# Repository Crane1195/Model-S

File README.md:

# Model-S
This circuit board is a complete solution for making custom all digital GameCube controllers without soldering.

## Features
- Connects to GameCube/Wii/GCC to USB adapter using the USB-C to GameCube cables that are sold on the Frame1 and the B0XX websites
- Connect buttons with screw terminals or 2.54mm pitch through holes
- Easily connect to a Brook Board to use the controller on PlayStation/Xbox/other consoles, with both boards sharing the Model S USB-C port
- Can be powered with just 3.3V, allowing the board to work on Mayflash adapters without the gray USB cable as well as GameCube/Wii consoles with faulty rumble lines

## Resources

User Manual - https://www.craneslab.xyz/manuals/s

Firmware - https://github.com/Crane1195/CL-FW

Questions - https://craneslab.xyz/discord

## License
This project is licenced under the GNU GPL Version 3. [See the included LICENSE file for details](LICENSE).

## Support my work
I set up a donation link for people who appreciate my work and wish to donate. Donations are greatly appreciated, but are far from necessary:

https://www.paypal.com/donate/?hosted_button_id=NFDEML5FKR8N8

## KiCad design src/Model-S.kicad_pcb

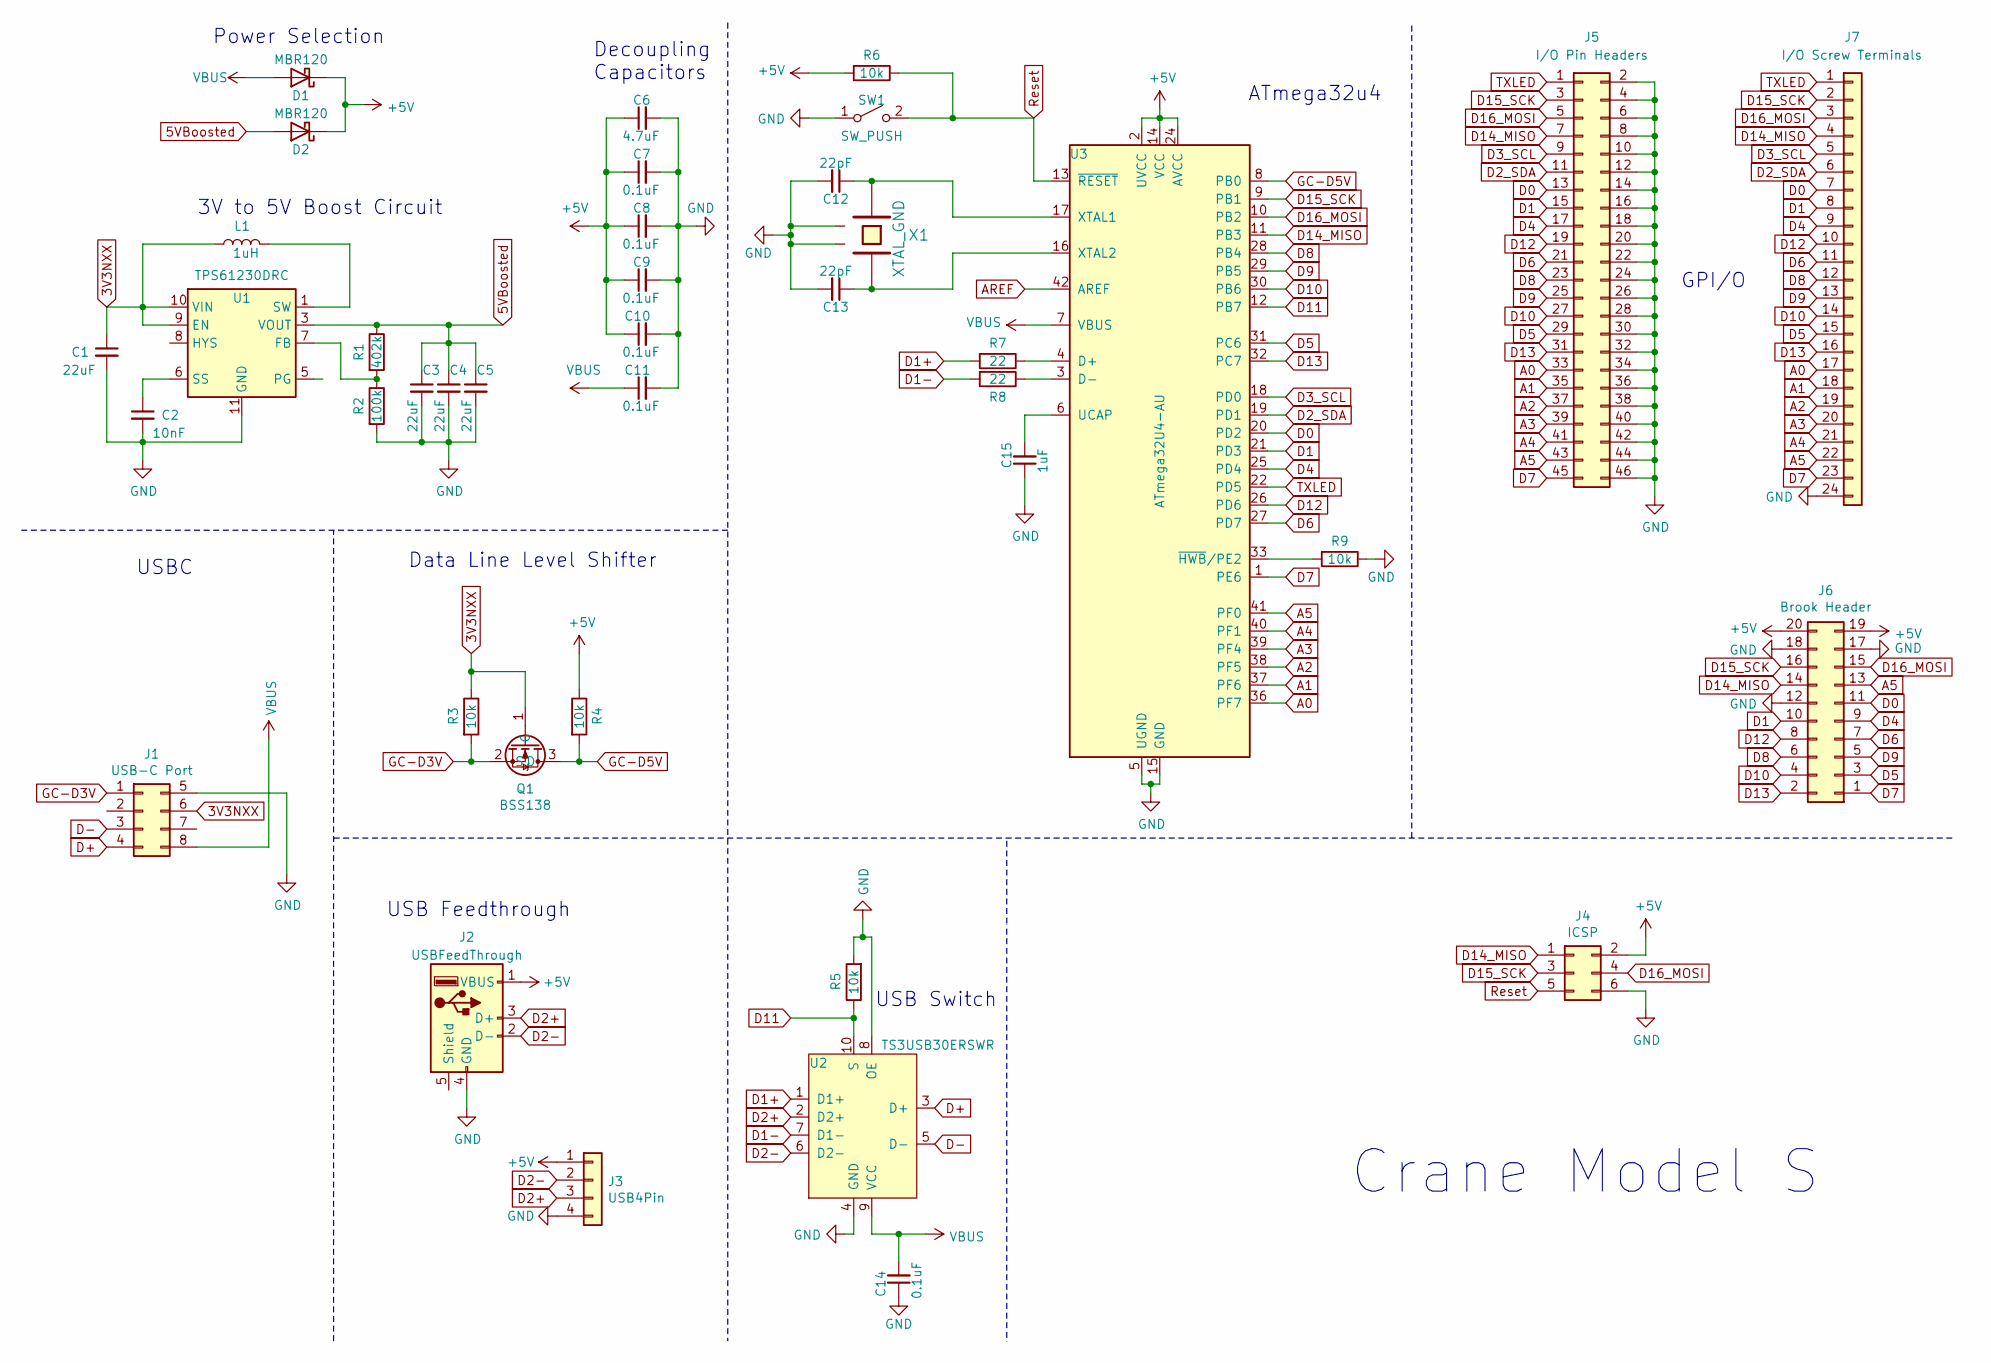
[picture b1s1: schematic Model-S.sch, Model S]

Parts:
C1, C3, C4, C5: 22uF; C_0805_2012Metric_Pad1.18x1.45mm_HandSolder
C2: 10nF; C_0805_2012Metric_Pad1.18x1.45mm_HandSolder
C6: 4.7uF; C_0805_2012Metric_Pad1.18x1.45mm_HandSolder
C7, C8, C9, C10, C11, C14: 0.1uF; C_0805_2012Metric_Pad1.18x1.45mm_HandSolder
C12, C13: 22pF; C_0805_2012Metric_Pad1.18x1.45mm_HandSolder
C15: 1uF; C_0805_2012Metric_Pad1.18x1.45mm_HandSolder
D1, D2: MBR120; D_SOD-123
J1: USB-C Port; Crane_USBC
J2: USBFeedThrough; USB_A_Female_UE27AC54100
J3: USB4Pin; PinHeader_1x04_P2.54mm_Vertical
J4: ICSP; PinHeader_2x03_P2.54mm_Vertical
J5: I/O Pin Headers; PinHeader_2x23_P2.54mm_Vertical
J6: Brook Header; PinHeader_2x10_P2.54mm_Vertical
J7: I/O Screw Terminals; 24PinScrewTerminal
L1: 1uH; L_1008_2520Metric
Q1: BSS138; SOT-23
R1: 402k; R_0805_2012Metric_Pad1.20x1.40mm_HandSolder
R2: 100k; R_0805_2012Metric_Pad1.20x1.40mm_HandSolder
R3, R4, R5, R6, R9: 10k; R_0805_2012Metric_Pad1.20x1.40mm_HandSolder
R7, R8: 22; R_0805_2012Metric_Pad1.20x1.40mm_HandSolder
SW1: SW_PUSH; SW_SPST_TL3342
U1: TPS61230DRC; Texas_S-PVSON-N10_ThermalVias
U2: TS3USB30ERSWR; UQFN-10_1.4x1.8mm_P0.4mm
U3: ATmega32U4-AU; TQFP-44_10x10mm_P0.8mm
X1: XTAL_GND; Crystal_SMD_TXC_7M-4Pin_3.2x2.5mm

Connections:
3V3NXX: C1.1, J1.6, L1.1, Q1.1 (G), R3.1, U1.9 (EN), U1.10 (VIN)
5VBoosted: C3.1, C4.1, C5.1, D2.2 (A), R1.1, U1.3 (VOUT), U1.4 (VOUT)
+5V: C6.1, C7.1, C8.1, C9.1, C10.1, D1.1 (K), D2.1 (K), J2.1 (VBUS), J3.1, J4.2, J6.19, J6.20, R4.1, R6.2, U3.2 (UVCC), U3.14 (VCC), U3.24 (AVCC), U3.34 (VCC), U3.44 (AVCC)
A0: J5.33, J7.17, U3.36 (PF7)
A1: J5.35, J7.18, U3.37 (PF6)
A2: J5.37, J7.19, U3.38 (PF5)
A3: J5.39, J7.20, U3.39 (PF4)
A4: J5.41, J7.21, U3.40 (PF1)
A5: J5.43, J6.13, J7.22, U3.41 (PF0)
AREF: U3.42 (AREF)
D0: J5.13, J6.11, J7.7, U3.20 (PD2)
D1: J5.15, J6.10, J7.8, U3.21 (PD3)
D1+: R7.2, U2.1 (D1+)
D1-: R8.2, U2.7 (D1-)
D2+: J2.3 (D+), J3.3, U2.2 (D2+)
D2-: J2.2 (D-), J3.2, U2.6 (D2-)
D2_SDA: J5.11, J7.6, U3.19 (PD1)
D3_SCL: J5.9, J7.5, U3.18 (PD0)
D4: J5.17, J6.9, J7.9, U3.25 (PD4)
D5: J5.29, J6.3, J7.15, U3.31 (PC6)
D6: J5.21, J6.7, J7.11, U3.27 (PD7)
D7: J5.45, J6.1, J7.23, U3.1 (PE6)
D8: J5.23, J6.6, J7.12, U3.28 (PB4)
D9: J5.25, J6.5, J7.13, U3.29 (PB5)
D10: J5.27, J6.4, J7.14, U3.30 (PB6)
D11: R5.1, U2.10 (S), U3.12 (PB7)
D12: J5.19, J6.8, J7.10, U3.26 (PD6)
D13: J5.31, J6.2, J7.16, U3.32 (PC7)
D14_MISO: J4.1, J5.7, J6.14, J7.4, U3.11 (PB3)
D15_SCK: J4.3, J5.3, J6.16, J7.2, U3.9 (PB1)
D16_MOSI: J4.4, J5.5, J6.15, J7.3, U3.10 (PB2)
D+: J1.4, U2.3 (D+)
D-: J1.3, U2.5 (D-)
GC-D3V: J1.1, Q1.2 (S), R3.2
GC-D5V: Q1.3 (D), R4.2, U3.8 (PB0)
GND: C1.2, C2.2, C3.2, C4.2, C5.2, C6.2, C7.2, C8.2, C9.2, C10.2, C11.2, C12.2, C13.2, C14.1, C15.1, J1.5, J2.4 (GND), J3.4, J4.6, J5.2, J5.4, J5.6, J5.8, J5.10, J5.12, J5.14, J5.16, J5.18, J5.20, J5.22, J5.24, J5.26, J5.28, J5.30, J5.32, J5.34, J5.36, J5.38, J5.40, J5.42, J5.44, J5.46, J6.12, J6.17, J6.18, J7.24, R2.2, R5.2, R9.1, SW1.1 (A), U1.11 (GND), U2.4 (GND), U2.8 (OE), U3.5 (UGND), U3.15 (GND), U3.23 (GND), U3.35 (GND), U3.43 (GND), X1.2, X1.4
unnamed: C2.1, U1.6 (SS)
unnamed: C12.1, U3.17 (XTAL1), X1.1
unnamed: C13.1, U3.16 (XTAL2), X1.3
unnamed: C15.2, U3.6 (UCAP)
unnamed: L1.2, U1.1 (SW), U1.2 (SW)
unnamed: R1.2, R2.1, U1.7 (FB)
unnamed: R7.1, U3.4 (D+)
unnamed: R8.1, U3.3 (D-)
unnamed: R9.2, U3.33 (~HWB~/PE2)
Reset: J4.5, R6.1, SW1.2 (B), U3.13 (~RESET)
TXLED: J5.1, J7.1, U3.22 (PD5)
VBUS: C11.1, C14.2, D1.2 (A), J1.8, U2.9 (VCC), U3.7 (VBUS)

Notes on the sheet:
Power Selection
ATmega32u4
GPI/O
USB Feedthrough
3V to 5V Boost Circuit
USB Switch
Data Line Level Shifter
Decoupling Capacitors
Crane Model S
USBC

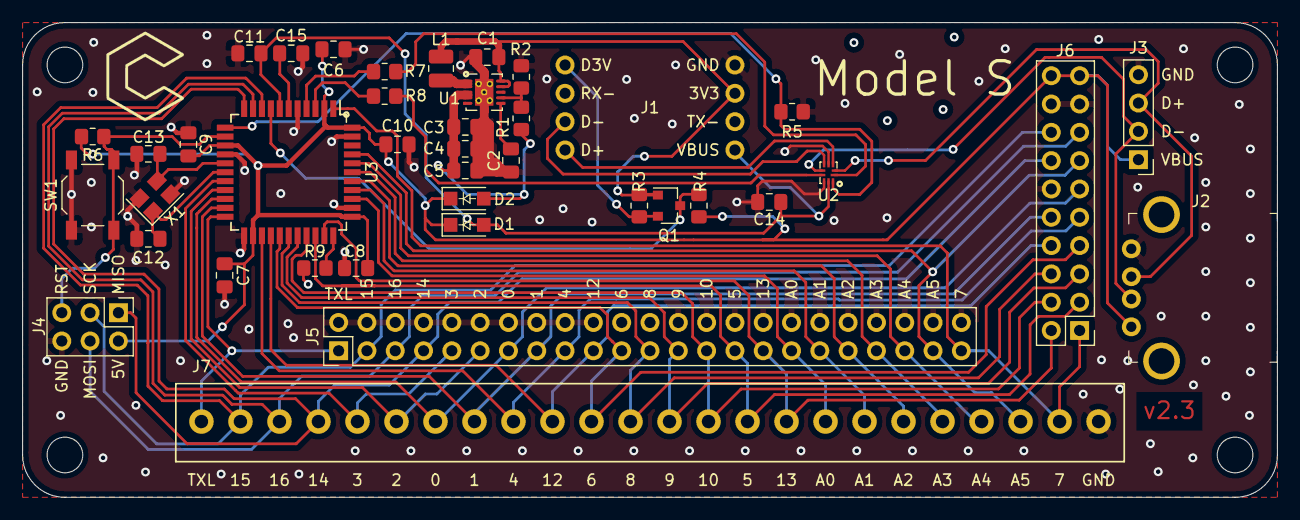
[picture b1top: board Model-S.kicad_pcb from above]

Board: 2 copper layers, 112.6 x 42.6 mm, 40 parts (0 on the bottom side), 47 nets.

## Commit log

2022-03-05 GCCPCB 2.0
2022-03-05 Model S 2.1
2022-03-05 Model S 2.2
2022-03-05 Model S 2.3
